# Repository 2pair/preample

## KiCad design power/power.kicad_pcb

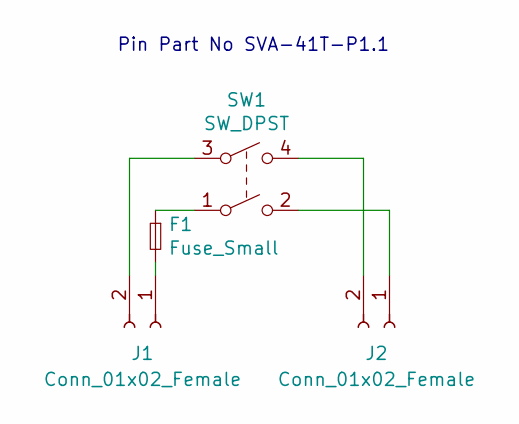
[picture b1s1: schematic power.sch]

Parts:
F1: Fuse_Small; Keystone 4628 Fuse Holder
J1, J2: Conn_01x02_Female; B2P3-VH
SW1: SW_DPST; E-Switch_P227EE1CXC

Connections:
unnamed: F1.1, SW1.1
unnamed: F1.2, J1.1
unnamed: J1.2, SW1.3
unnamed: J2.1, SW1.2
unnamed: J2.2, SW1.4

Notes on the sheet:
Pin Part No SVA-41T-P1.1

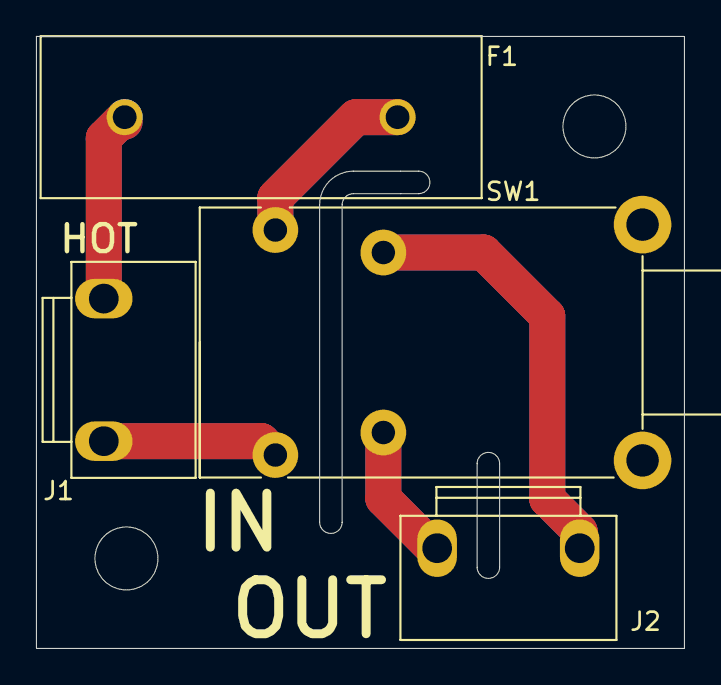
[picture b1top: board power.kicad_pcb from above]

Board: 2 copper layers, 36.0 x 34.0 mm, 4 parts (0 on the bottom side), 5 nets.

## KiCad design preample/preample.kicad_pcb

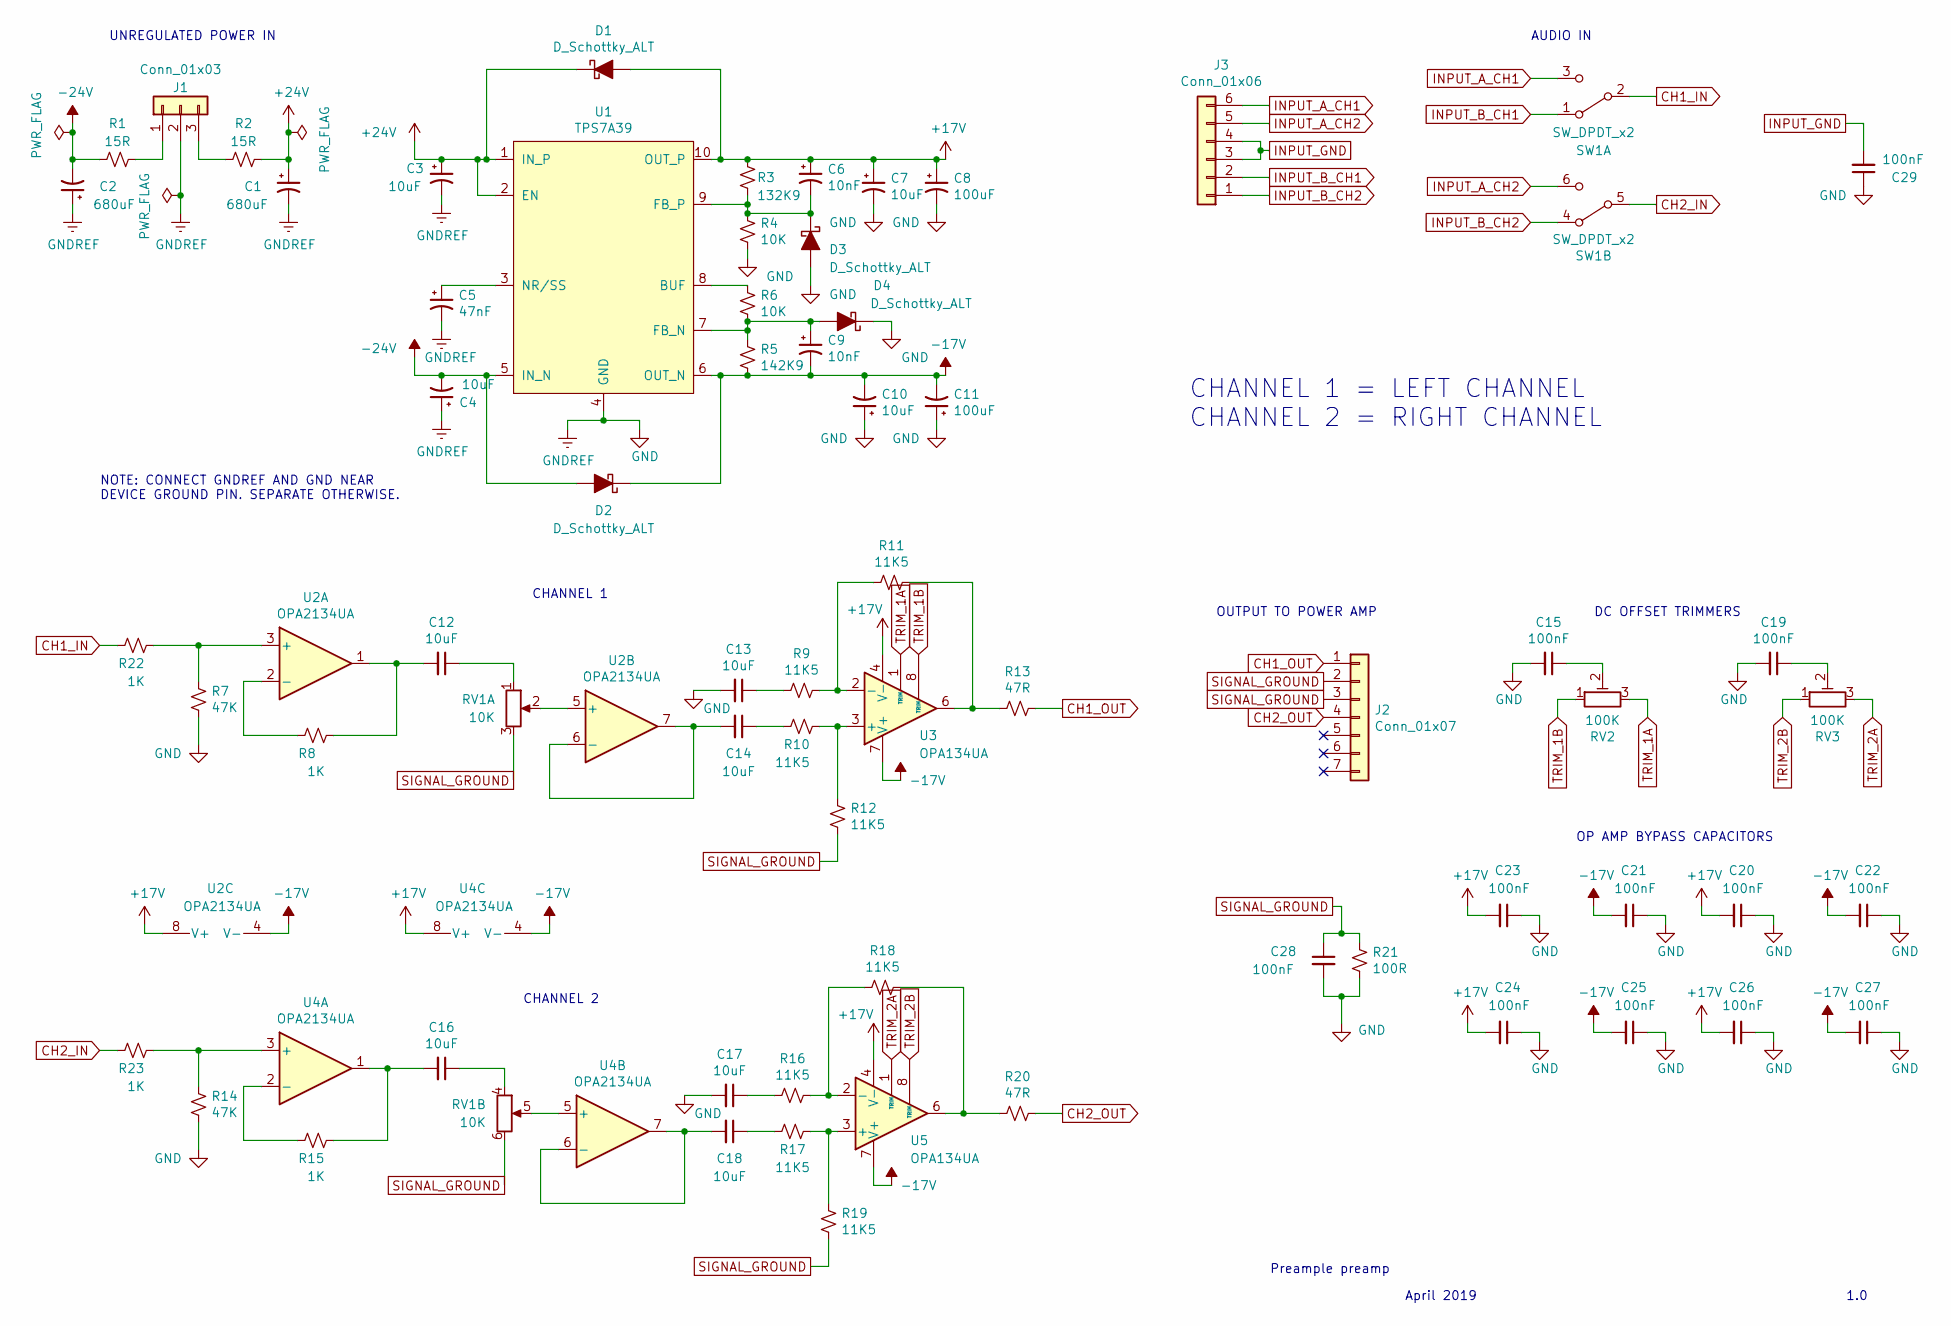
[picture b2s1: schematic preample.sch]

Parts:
C1, C2: 680uF; EEV-FK1H681M; Part No EEV-FK1H681M
C3, C4, C7, C10: 10uF; C_1206_3216Metric; Part No CL31B106KBHNNNE
C5: 47nF; C_0402_1005Metric; Part No GRM155R71E473KA88D
C6, C9: 10nF; C_0402_1005Metric; Part No CL05B103KB5NNNC
C8, C11: 100uF; PCR1E101MCL1GS; Part No PCR1E101MCL1GS
C12, C13, C14, C16, C17, C18: 10uF; MKS2B051001N00JSSD; Part No MKS2B051001N00JSSD
C15, C19, C20, C21, C22, C23, C24, C25, C26, C27: 100nF; C_0603_1608Metric; Part No CL10B104KB8NNNC
C28, C29: 100nF; SMDTD03100TA00KQ00; Part No SMDTD03100TA00KQ00
D1, D2, D3, D4: D_Schottky_ALT; D_SOD-323F; Part No RB751V-40WS RRG
J1: Conn_01x03; JST_PH_B3B-PH-K_1x03_P2.00mm_Vertical; Part No B3B-PH-K-S(LF)(SN)
J2: Conn_01x07; JST_PH_B7B-PH-K_1x07_P2.00mm_Vertical; Part No B7B-PH-K-S(LF)(SN)
J3: Conn_01x06; JST_PH_B6B-PH-K_1x06_P2.00mm_Vertical; Part No B6B-PH-K-S(LF)(SN)
R1, R2: 15R; R_2512_6332Metric; Part No RPC2512JT15R0
R3: 132K9; R_0402_1005Metric; Part No ERJ-2RKF1333X
R4, R6: 10K; R_0402_1005Metric; Part No ERJ-2RKF1002X
R5: 142K9; R_0402_1005Metric; Part No ERJ-2RKF1433X
R7, R14: 47K; R_0805_2012Metric; Part No ERA-6AEB473V
R8, R15, R22, R23: 1K; R_0805_2012Metric; Part No ERA-6AEB102V
R9, R10, R11, R12, R16, R17, R18, R19: 11K5; R_0805_2012Metric; Part No ERA-6AEB1152V
R13, R20: 47R; R_0805_2012Metric; Part No ERA-6AEB470V
R21: 100R; R_0805_2012Metric; Part No ERA-6AEB101V
RV1: 10K; RK271 10KAX2
RV2, RV3: 100K; 22AR100KLFTR; Part No 22AR100KLFTR
SW1: SW_DPDT_x2; PBH2UEENAGX
U1: TPS7A39
U2, U4: OPA2134UA; SOIC-8_3.9x4.9mm_P1.27mm
U3, U5: OPA134UA; SOIC-8_3.9x4.9mm_P1.27mm

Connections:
+15V: C6.1, C7.1, C8.1, C20.2, C23.2, C24.2, C26.2, D1.2 (A), R3.1, U1.10 (OUT_P), U2.8 (V+), U3.4 (V-), U4.8 (V+), U5.4 (V-)
+24V: C1.1, C3.1, D1.1 (K), R2.2, U1.1 (IN_P), U1.2 (EN)
-15V: C9.2, C10.2, C11.2, C21.2, C22.2, C25.2, C27.2, D2.1 (K), R5.2, U1.6 (OUT_N), U2.4 (V-), U3.7 (V+), U4.4 (V-), U5.7 (V+)
-24V: C2.2, C4.2, D2.2 (A), R1.1, U1.5 (IN_N)
CH1_IN: R22.1, SW1.2 (B)
CH1_OUT: J2.1, R13.2
CH2_IN: R23.1, SW1.5 (B)
CH2_OUT: J2.4, R20.1
GND: C1.2, C2.1, C3.2, C4.1, C5.2, C7.2, C8.2, C10.1, C11.1, C13.2, C15.2, C17.2, C19.2, C20.1, C21.1, C22.1, C23.1, C24.1, C25.1, C26.1, C27.1, C28.2, C29.1, D3.2 (A), D4.1 (K), J1.2, R4.2, R7.1, R14.1, R21.2, U1.4 (GND)
INPUT_A_CH1: J3.6, SW1.3 (C)
INPUT_A_CH2: J3.5, SW1.6 (C)
INPUT_B_CH1: J3.2, SW1.1 (A)
INPUT_B_CH2: J3.1, SW1.4 (A)
INPUT_GND: C29.2, J3.3, J3.4
unnamed: C5.1, U1.3 (NR/SS)
unnamed: C6.2, D3.1 (K), R3.2, R4.1, U1.9 (FB_P)
unnamed: C9.1, D4.2 (A), R5.1, R6.2, U1.7 (FB_N)
unnamed: C12.1, RV1.1
unnamed: C12.2, R8.2, U2.1
unnamed: C13.1, R9.2
unnamed: C14.1, R10.1
unnamed: C14.2, U2.6 (-), U2.7
unnamed: C15.1, RV2.2
unnamed: C16.1, RV1.4
unnamed: C16.2, R15.2, U4.1
unnamed: C17.1, R16.2
unnamed: C18.1, R17.1
unnamed: C18.2, U4.6 (-), U4.7
unnamed: C19.1, RV3.2
unnamed: J1.1, R1.2
unnamed: J1.3, R2.1
unnamed: R6.1, U1.8 (BUF)
unnamed: R8.1, U2.2 (-)
unnamed: R10.2, R12.2, U3.3 (+)
unnamed: R11.1, R13.1, U3.6
unnamed: R9.1, R11.2, U3.2 (-)
unnamed: R14.2, R23.2, U4.3 (+)
unnamed: R15.1, U4.2 (-)
unnamed: R16.1, R18.2, U5.2 (-)
unnamed: R17.2, R19.2, U5.3 (+)
unnamed: R18.1, R20.2, U5.6
unnamed: R7.2, R22.2, U2.3 (+)
unnamed: RV1.2, U2.5 (+)
unnamed: RV1.5, U4.5 (+)
SIGNAL_GROUND: C28.1, J2.2, J2.3, R12.1, R19.1, R21.1, RV1.3, RV1.6
TRIM_1A: RV2.3, U3.1 (TRIM)
TRIM_1B: RV2.1, U3.8 (TRIM)
TRIM_2A: RV3.3, U5.1 (TRIM)
TRIM_2B: RV3.1, U5.8 (TRIM)

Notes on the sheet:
DC OFFSET TRIMMERS
UNREGULATED POWER IN
Preample preamp
April 2019
1.0
OP AMP BYPASS CAPACITORS
OUTPUT TO POWER AMP
NOTE: CONNECT GNDREF AND GND NEAR DEVICE GROUND PIN. SEPARATE OTHERWISE.
CHANNEL 1
CHANNEL 2
AUDIO IN
CHANNEL 1 = LEFT CHANNEL CHANNEL 2 = RIGHT CHANNEL

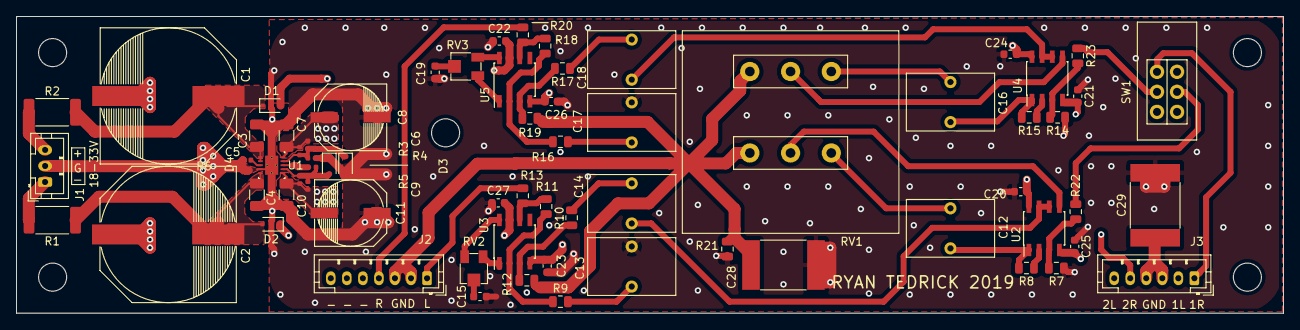
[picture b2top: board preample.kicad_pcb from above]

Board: 4 copper layers, 158.0 x 37.0 mm, 68 parts (0 on the bottom side), 49 nets.

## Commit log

2019-04-23 :octocat: Added .gitattributes & .gitignore files
2019-04-23 Basics of schematic mostly in place
2019-04-29 changed op amps. changed rail voltages. hooked up bypass caps for op amps. additional passives for noise reduction in op amp circuits.
    separated the signal grounds. Need to do more research on if that is a
    normal thing. Added rca inputs, need to investigate if a simple switch
    is enough or if analog mux circuits are needed.
2019-05-01 added layout sketch. working on grounds. playing with connectors.
2019-05-07 Added switching circuit. Added power supply footprints. Started power supply layout.
2019-05-08 swapped 10uF psu caps for smaller ceramics. assigned footprints to many passives. more pcb layout.
2019-05-11 all footprints made except connectors. all signal traced laid.
2019-05-12 reorganized PCB to fit target chassis
2019-05-14 Fixed cap issue in schematic. finished pcb layout
2019-05-26 Changes resistors for opamps to 0805s. Chose more realistic power resistors. rerouted for new components.
2019-05-27 Added simulation. Added current path for negative feed forward cap. Chose resistors for amplifier circuits.
2019-05-27 starting design for faceplates/mechanical
2019-05-28 Drawing for back faceplate. Added F\fuse
2019-05-31 Added breakout board for power switch
2019-06-02 finished power breakout board. added input breakout board
2019-06-02 Reorganized repo. Added gerbers.
